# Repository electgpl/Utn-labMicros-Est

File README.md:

Estación Meteorológica Inalámbrica
=============================

### Introducción
 
Se presentará una estación meteorológica inalámbrica hogareña, la misma consta de dos dispositivos individuales, una estación meteorológica interna que provee de valores dentro del recinto donde se encuentra, y una estación meteorológica externa que provee los valores exteriores, entre ambos dispositivos se realiza la telemetría exterior y se muestra en un display alfanumérico en la estación interior, con la finalidad de observar a primera vista los datos meteorológicos internos y externos.
Esta estación funciona de forma inalámbrica con enlaces de radiofrecuencia y funciona con pilas primarias en el caso exterior y batería recargable en el caso interior.

El proyecto surge de la idea de practicar la programación en lenguaje C, los protocolos de comunicación serie y el transporte de los datos vía enlaces inalambricos, en este proyecto se abordará la estructura necesaria para realizar una trama de datos básica, su payload y verificación.
También se realizará la puesta en marcha del sistema mediante electrónica de bajo costo y bajo consumo para afrontar el problema energético que conlleva la utilización de pilas y baterías de forma competitiva con productos comerciales de la actualidad.

----------

----------

### Objetivos
 
- Estación meteorológica con medición interna y externa.
- La estación consiste en un sensor externo y uno interno. 
- El sensor externo posee la capacidad de medir Temperatura, Humedad y Luminosidad. 
- El sensor interno mide Temperatura y Humedad. 
- La telemetría se realiza mediante un enlace inalámbrico simplex UHF, el sensor externo funciona mediante celdas primarias alcalinas y posee electrónica de bajo consumo proporcionando una autonomía de 1 año.
- El sensor interno posee un display de LCD de 2 lineas y 16 caracteres que mostrará la Temperatura y Humedad del sensor interno, la Temperatura, Humedad y Luminosidad del sensor externo.
- El sensor interno cuenta con una batería secundaria de iones de litio recargable mediante un conector micro usb.

> **Nota:**
> - El microcontrolador utilizado se basa en core 8051 (para el cual el firmware se encuentra compilado con Keil sobre un microcontrolador de Silabs C8051F832).
> - Se ha realizado también para Microchip sobre diversas plataformas
> - La simulación se realiza para Microchip sobre Proteus.
> - Los diagramas, PCB y Gerber, son realizados con Eagle.

----------

### Diseño conceptual
 
Para realizar nuestra estación, utilizaremos microcontroladores modernos de bajo consumo y bajo costo, que permite trabajar con una buena autonomía utilizando pilas primarias para aumentar al máximo el rendimiento del sistema.
La estación meteorológica utilizara la función especial del microcontrolador para entrar en modo bajo consumo y así extender la batería.
Una vez en bajo consumo se despertara de forma automática mediante el WDT del microcontrolador cada 10 segundos, se tomará una muestra de temperatura, humedad y luminosidad, se enviará mediante el enlace de RF a la estación interna y luego se volverá a dormir entrando en bajo consumo.
El enlace se ha simplificado al máximo para reducir el costo, se utiliza modulación ASK en UHF mediante oscilador a cristal SAW de 433.92MHz y se enviaran los datos mediante UART invertida a 600bps.
En la estación interior, se utilizara la interrupción de dato presente en UART para atender la telemetría exterior, realizar el parse de la trama y dejarla disponible para la utilización.
Se tomará humedad y temperatura interior, y junto con la telemetría exterior se mostrará todo en un dsiplay LCD de 2x16 caracteres alfanuméricos.
La estación interna cuenta con baterías recargables y su controlador de carga para ser conectado directamente con un cable estándar micro usb.

----------
## Implementación
### Especificaciones de Hardware:
#### Dispositivo Interno:
- Sensor de Temperatura y Humedad, DHT11 (comunicación onWire propietaria).
- Receptor modular RWS simplex UHF operando en la banda de 70cm en 433.92MHz, modulación ASK OOK utilizando protocolo RS232, Antena del tipo microstrip IFA 50 Ohms.
- Display LCD 2x16 con controlador HD44780, para mostrar Temp, Hum, (Interna y Externa), Luminosidad (Externa).
- Cargador de Batería tipo Secundaria Li-Ion con micro USB basado en controlador TP4056, Celda 18650, 4800mAh (típico) .
- Microcontrolador de 8bit Silabs C8051F832.
- Circuito impreso hasta 2 Layer con PTH y tecnologia SMD. 
- Aceptación IPC-356, IPC-600, UL-94.

#### Dispositivo Externo:
- Sensor de Temperatura y Humedad, DHT11 (comunicación onWire propietaria).
- Sensor de Luminosidad basado en LDR con acondicionamiento por firmware.
- Transmisor modular TWS simplex UHF operando en la banda de 70cm en 433.92MHz, modulación ASK OOK utilizando protocolo RS232, Antena del tipo microstrip IFA 50 Ohms.
- Batería del tipo primaria alcalina ZnMnO2 tamaño AA, 2500mAh (típico).
- Microcontrolador de 8bit Silabs C8051F832.
- Circuito impreso hasta 2 Layer con PTH y tecnologia SMD. 
- Aceptación IPC-356, IPC-600, UL-94.

### Especificaciones de Firmware:
El firmware debe contar con estándares de programación, encabezado del programa, descripción, autores, versionado, fechas y referencias.
Las funciones deben contar con los valores de ingreso y egreso a la misma como así el tipo de datos y la descripción de la función.
El programa se realizará en lenguaje C.

- Desarrollo de Bibliotecas necesarias (Estandarizado)
- Pruebas Unitarias de cada Biblioteca con el hardware asociado
- Desarrollo de programa principal
- Manejo de errores
- Creación de diagramas de flujo o estado
- Pruebas Integrados del firmware con todas las Bibliotecas y devices

-------
- Biblioteca para sensor DHT11
>- Manejo de Bus OneWire 5 bytes (4 bytes de datos 1 byte de checksum)
>- Formateo de datos de salida Temperatura: entero sin signo de 8bit
>- Formateo de datos de salida Humedad: entero sin signo de 8bit

- Biblioteca de control del LCD
>- Mapeo de los 2 renglones y 16 caracteres.
>- Control de memoria mediante bus de 4bit y control.
>- Entrada mediante string con control xy de caracteres.

- Biblioteca bitbanging para protocolo manchester en los enlaces UHF
>- BitBanging de del protocolo.
>- Realización de Checksum
>- Salida de datos en formato hexadecimal.
>- Entrada de datos en formato hexadecimal.

- Biblioteca del sensor de luminosidad
>- Utilización del conversor analogico digital provisto por el microcontrolador.
>- Configuración de baja velocidad a resolución de 8bit.
>- Salida datos en formato entero.

- Manejo de Baja Energía
>- Apagado de dispositivos periféricos en desuso mediante transistores NMOS.
>- Reloj WDT para función WakeUp del MCU cada 2.3s
>- Si los datos a medir (sensores) no cambian respecto a la medición anterior, no se enviaran datos repetidos mejorando el consumo.

--------

### Especificaciones Técnicas:

Rango de temperatura 0-50°c (precisión ±2°c) 
Rango de humedad 20-90%RH (precisión ±5％) 
Rango de luminosidad 0-100% (precisión ±20％)    
Rango de trabajo hasta 20m Frecuencia de trabajo 433MHz 
Batería de sensor 2xAA Alcalina 
Vida útil de 2 años 
Batería de cuerpo 1x18650
Vida útil Recargable via USB 
Medidas cuerpo 113x67x27.5mm 
Medidas Sensor 91x70x32.5mm 
Gabinete exterior IPX3 
Este equipo no dispone de protección ATEX, por lo que no debe ser usado en atmósferas potencialmente explosivas (polvo, gases inflamables).

--------

### Conclusiones
 
Se ha logrado implementar una estación meteorológica hogareña de bajo consumo y bajo costo que presenta una propuesta comercial respecto a las competidoras de mismas prestaciones.

Se implementó el código necesario para realizar el proyecto sobre core 8051 bajo una plataforma moderna que opera en 16MHz y 16MIPS.
Se realizó todo el tratamiento de la trama, preámbulo, payload, checksum y parseo de datos para realizar el enlace de telemetría entre los dos dispositivos.
Se analizó la velocidad de transferencia de datos sobre UART para lograr la mejor comunicación y alcance sobre módulos de RF de bajo costo.
Se comprobó el diseño de la antena con la ayuda de instrumental adecuado “VNA” para su correcta adaptación.

--------

### Bibliografía
 
- [1] “Manual 8051 Keil”, 
http://www.keil.com/support/man/docs/is51/
- [2] “Manual Eagle”, 
http://hades.mech.northwestern.edu/images/b/b4/Eagle_Manual.pdf
- [3] “Norma ATEX”, 
http://www.insht.es/InshtWeb/Contenidos/Normativa/GuiasTecnicas/Ficheros/ATM%C3%93SFERAS%20EXPLOSIVAS.pdf
- [4] “Norma IPX3”, 
http://hades.mech.northwestern.edu/images/b/b4/Eagle_Manual.pdfhttp://www.f2i2.net/documentos/lsi/rbt/guias/guia_bt_anexo_1_sep03R1.pdf
- [5] “Norma IPC610”, 
http://www.ipc.org/TOC/IPC-A-610E-Spanish.pdf
- [6] “Datasheet DHT11”, 
https://akizukidenshi.com/download/ds/aosong/DHT11.pdf
- [7] “Datasheet Modulos Transmisor y Receptor RF UHF”, https://4.imimg.com/data4/AJ/NM/MY-1833510/rf-transmitter-receiver-pair-433-mhz-ask.pdf
- [8] “Datasheet LDR”, 
http://kennarar.vma.is/thor/v2011/vgr402/ldr.pdf
- [9] “Datasheet C8051F832 Silabs”, https://www.silabs.com/documents/public/data-sheets/C8051F80x-83x.pdf
- [10] “Datasheet TP4056”, https://dlnmh9ip6v2uc.cloudfront.net/datasheets/Prototyping/TP4056.pdf

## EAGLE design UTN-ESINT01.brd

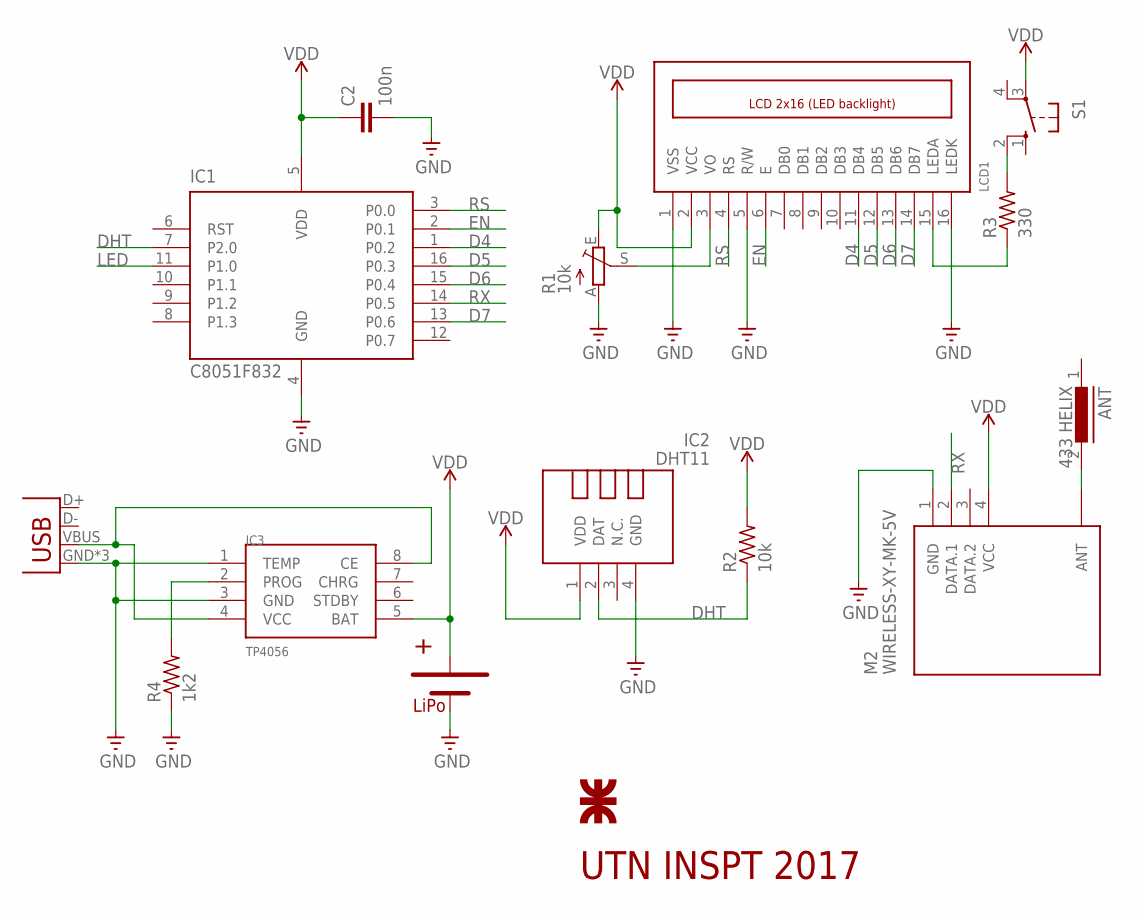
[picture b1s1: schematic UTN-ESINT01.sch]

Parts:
ANT: 433 HELIX; SMSC20
C2: 100n; C050-024X044
IC1: C8051F832; SOIC16R
IC2: DHT11; TEMP-HUM-SENSOR-DHT11
IC3: TP4056; SOP-8
LCD1: LCD_2X16_SIL; HY-1602F
M2: WIRELESS-XY-MK-5V
R1: 10k; B64Y
R2: 10k; 0207/10
R3: 330; 0207/10
R4: 1k2; 0207/10
S1: 10-XX; B3F-10XX
U$3: UTN_LOGO
U$4: LiPo; BATTERYPAD
X1: USB-MICROB

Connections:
D4: IC1.1 (P0.2), LCD1.11 (DB4)
D5: IC1.16 (P0.3), LCD1.12 (DB5)
D6: IC1.15 (P0.4), LCD1.13 (DB6)
D7: IC1.13 (P0.6), LCD1.14 (DB7)
DHT: IC1.7 (P2.0), IC2.2 (DAT), R2.1
EN: IC1.2 (P0.1), LCD1.6 (E)
GND: C2.2, IC1.4 (GND), IC2.4 (GND), IC3.1 (TEMP), IC3.3 (GND), LCD1.1 (VSS), LCD1.5 (R/W), LCD1.16 (LEDK), M2.1 (GND), R1.A, R4.1, U$4.-VE, X1.GND, X1.MT1 (GND), X1.MT2 (GND)
LED: IC1.11 (P1.0)
unnamed: ANT.2, M2.ANT
unnamed: IC3.4 (VCC), IC3.8 (CE), X1.VBUS
unnamed: LCD1.3 (VO), R1.S
unnamed: LCD1.15 (LEDA), R3.1
unnamed: R3.2, S1.2 (S1)
unnamed: IC3.2 (PROG), R4.2
RS: IC1.3 (P0.0), LCD1.4 (RS)
RX: IC1.14 (P0.5), M2.2 (DATA.1)
VDD: C2.1, IC1.5 (VDD), IC2.1 (VDD), IC3.5 (BAT), LCD1.2 (VCC), M2.4 (VCC), R1.E, R2.2, S1.3, U$4.+VE

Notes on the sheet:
UTN INSPT 2017
LiPo

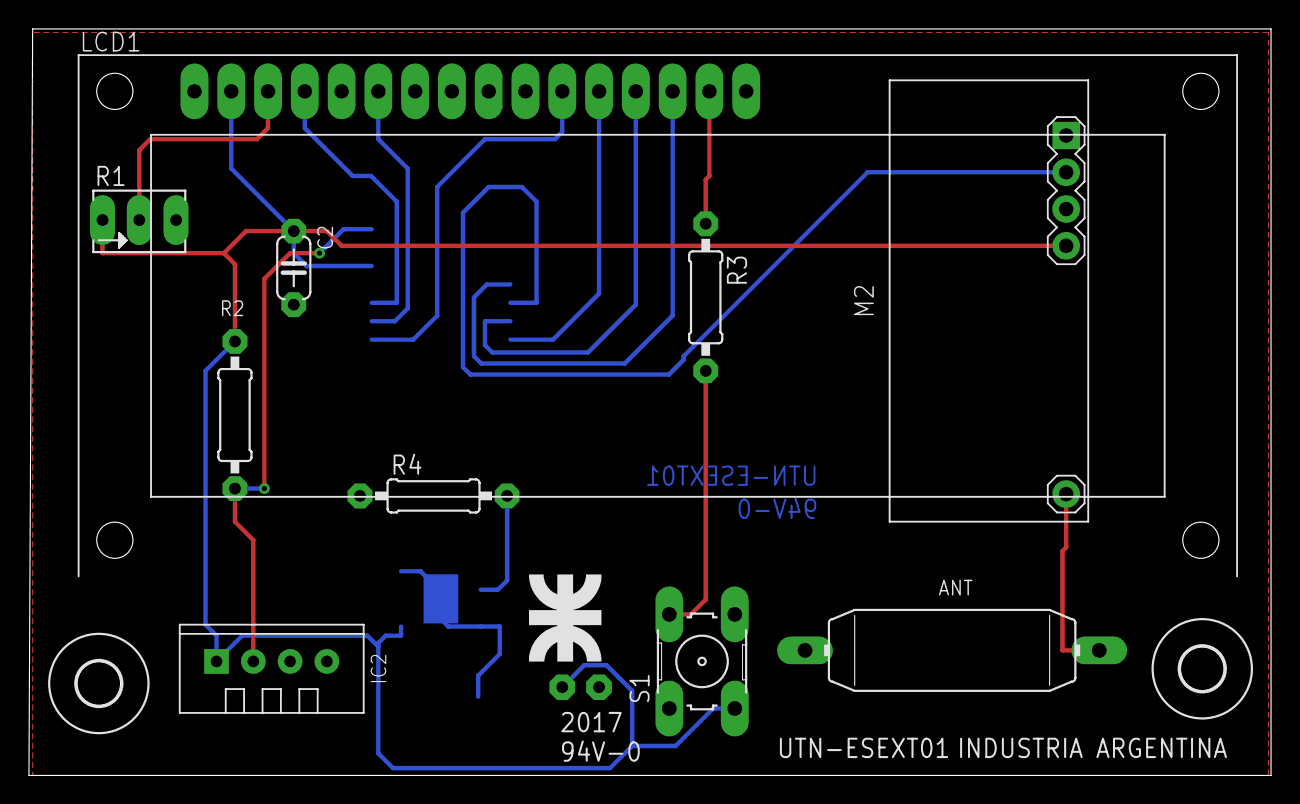
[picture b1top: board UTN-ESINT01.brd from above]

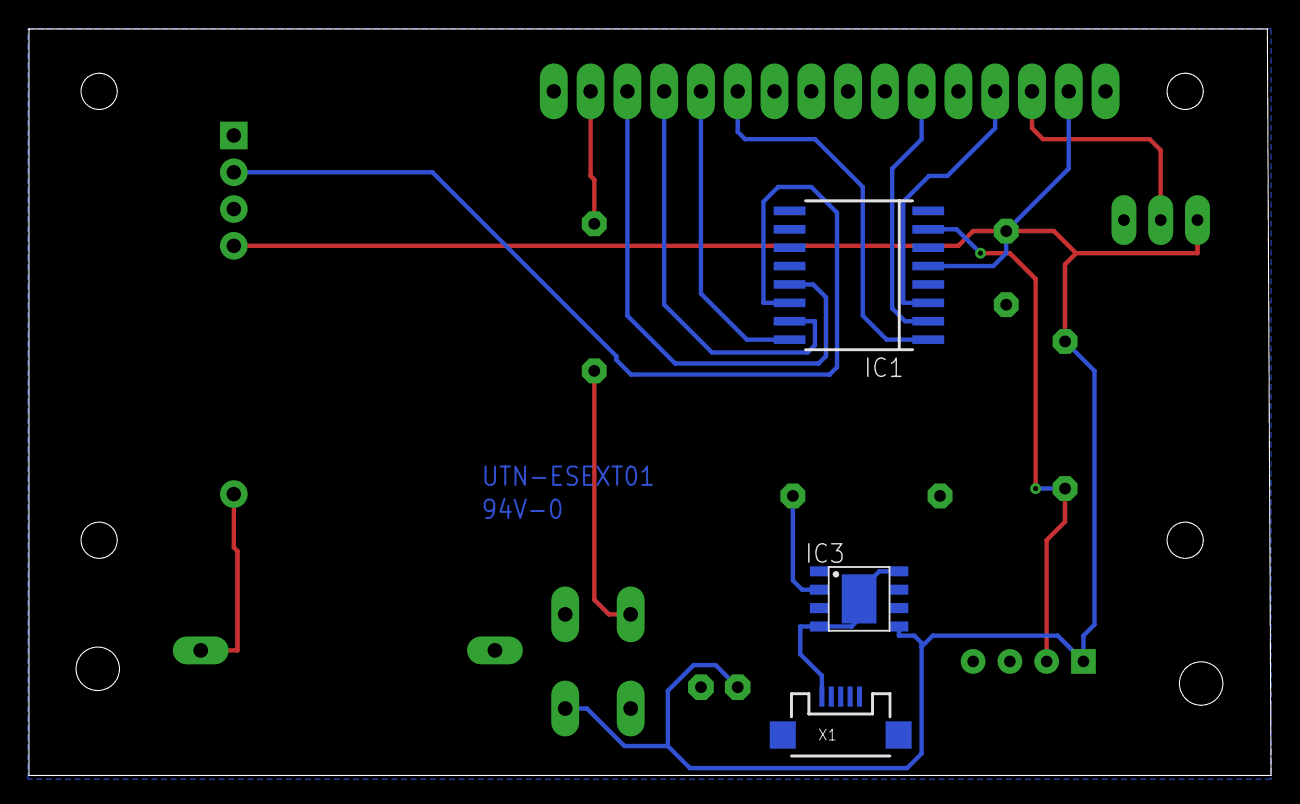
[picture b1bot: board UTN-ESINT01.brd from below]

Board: 2 copper layers, 85.8 x 51.6 mm, 17 parts (3 on the bottom side), 16 nets.

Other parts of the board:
U$1, U$2: 3,0

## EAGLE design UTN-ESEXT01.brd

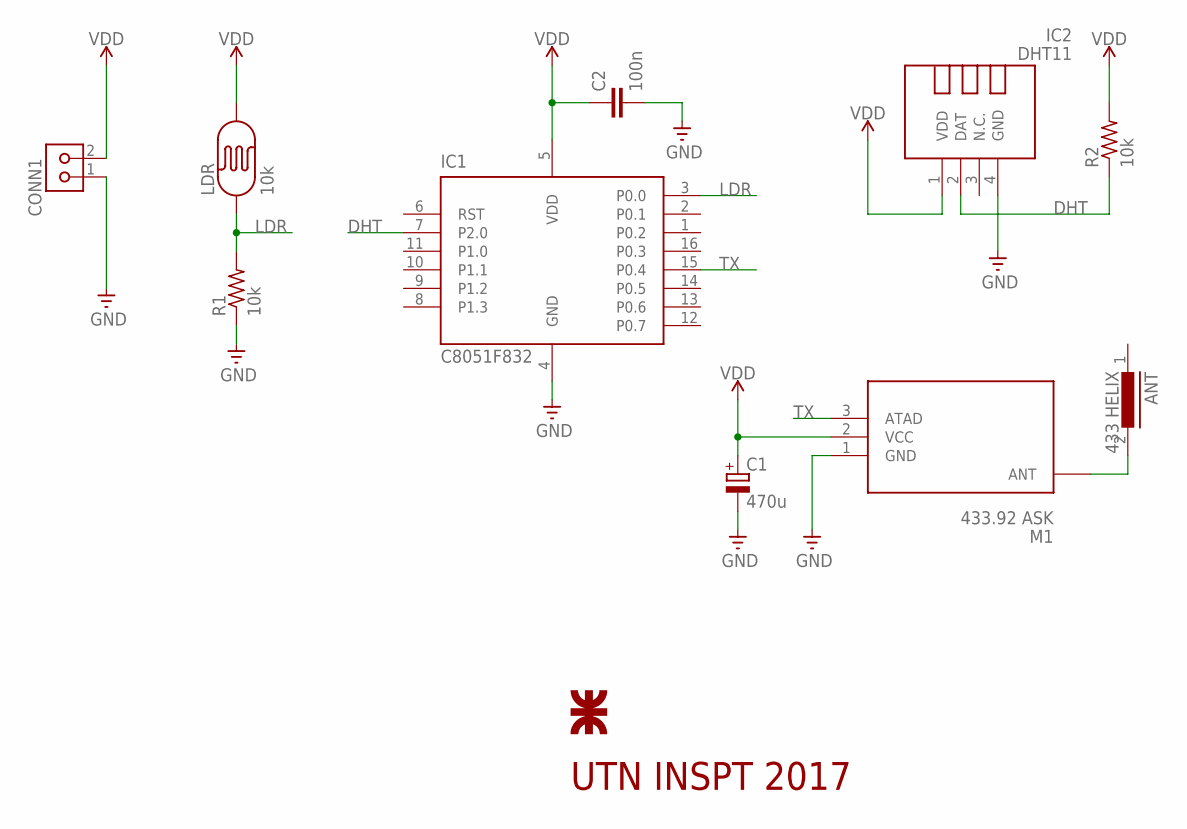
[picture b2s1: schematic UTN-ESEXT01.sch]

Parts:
ANT: 433 HELIX; SMSC20
C1: 470u; E3,5-10
C2: 100n; C050-024X044
CONN1: KK2VSQ; KK-V-2-SQ
IC1: C8051F832; SOIC16R
IC2: DHT11; TEMP-HUM-SENSOR-DHT11
LDR: 10k; ON_BOARD
M1: 433.92 ASK; WIRELESS-XY-FST
R1, R2: 10k; 0207/10
U$3: UTN_LOGO

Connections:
DHT: IC1.7 (P2.0), IC2.2 (DAT), R2.1
GND: C1.-, C2.2, CONN1.1, IC1.4 (GND), IC2.4 (GND), M1.1 (GND), R1.1
LDR: IC1.3 (P0.0), LDR.1, R1.2
unnamed: ANT.2, M1.ANT
TX: IC1.15 (P0.4), M1.3 (ATAD)
VDD: C1.+, C2.1, CONN1.2, IC1.5 (VDD), IC2.1 (VDD), LDR.2, M1.2 (VCC), R2.2

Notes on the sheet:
UTN INSPT 2017

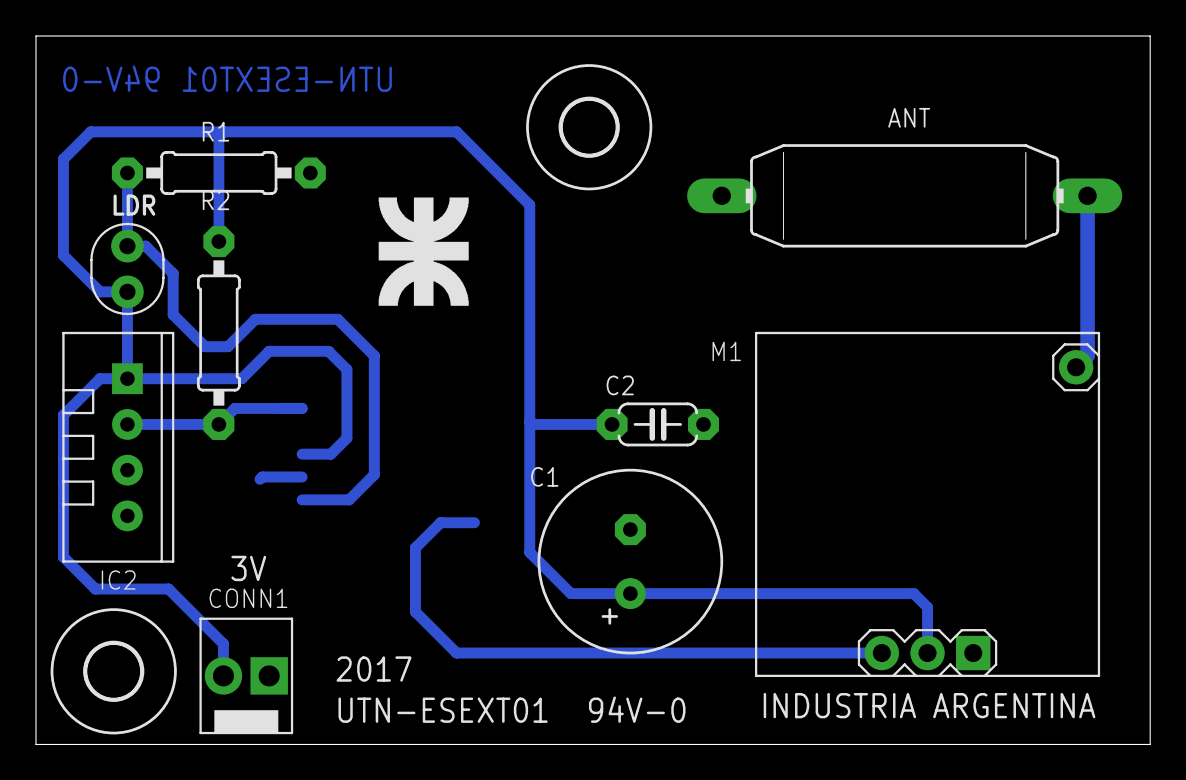
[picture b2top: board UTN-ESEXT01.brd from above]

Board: 2 copper layers, 61.9 x 39.4 mm, 13 parts (1 on the bottom side), 6 nets.

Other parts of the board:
U$1, U$2: 3,0

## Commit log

2017-10-12 Rename 8051 - Estacion Externa Silabs.c to firmware/8051 - Estacion Externa Silabs.c
2017-10-12 Rename 8051 - Estacion Interna Silabs.c to firmware/8051 - Estacion Interna Silabs.c
2017-10-12 Rename Documento Funcional - Estación Meteorológica - Final Entregable.gdoc to documentos/Documento Funcional - Estación Meteorológica - Final Entregable.gdoc
2017-10-12 Rename EQUIPO 3 TP presentado a Steiner.gdoc to documentos/EQUIPO 3 TP presentado a Steiner.gdoc
2017-10-12 Rename Manual de Usuario.gdoc to documentos/Manual de Usuario.gdoc
2017-10-12 Rename PIC - Estación Externa v1 - 1826 - HardTestOK.c to firmware/PIC - Estación Externa v1 - 1826 - HardTestOK.c
2017-10-12 Rename PIC - Estación Interna v1 - 883 - HardTestOK.hex to firmware/PIC - Estación Interna v1 - 883 - HardTestOK.hex
2017-10-12 Rename PIC - Estación Interna v1 - 883 - HardTestOK.c to firmware/PIC - Estación Interna v1 - 883 - HardTestOK.c
2017-10-12 Rename PIC - Estación Externa v1 - 1826 - HardTestOK.hex to firmware/PIC - Estación Externa v1 - 1826 - HardTestOK.hex
2017-10-12 Rename PIC - Estación Externa v1 - 676 - HardTestOK.c to firmware/PIC - Estación Externa v1 - 676 - HardTestOK.c
2017-10-12 Rename PIC - Estación Externa v1 - 676 - HardTestOK.hex to firmware/PIC - Estación Externa v1 - 676 - HardTestOK.hex
2017-10-12 Rename PIC - Estación Interna v1 - 1826 - HardTestOK.c to firmware/PIC - Estación Interna v1 - 1826 - HardTestOK.c
2017-10-12 Rename PIC - Estación Interna v1 - 1826 - HardTestOK.hex to firmware/PIC - Estación Interna v1 - 1826 - HardTestOK.hex
2017-10-12 Rename UTN-ESEXT01.brd to diagramas/UTN-ESEXT01.brd
2017-10-13 Rename UTN-ESINT01.sch to diagramas/UTN-ESINT01.sch
2017-10-13 Rename UTN-ESINT01.dsn to diagramas/UTN-ESINT01.dsn
2017-10-13 Rename UTN-ESINT01.brd to diagramas/UTN-ESINT01.brd
2017-10-13 Rename UTN-ESEXT01.sch to diagramas/UTN-ESEXT01.sch
2017-10-13 Rename diagramas/UTN-ESEXT01.brd to circuitos/UTN-ESEXT01.brd
2017-10-13 Rename diagramas/..UTN-ESEXT01.sch to circuitos/UTN-ESEXT01.sch
2017-10-13 Rename diagramas/UTN-ESINT01.brd to circuitos/UTN-ESINT01.brd
2017-10-13 Rename diagramas/UTN-ESINT01.sch to circuitos/UTN-ESINT01.sch
2017-10-13 Rename diagramas/UTN-ESINT01.dsn to circuitos/UTN-ESINT01.dsn
2017-11-08 modificaciones finales

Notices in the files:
parts and their libraries:
diy-modules: Released under the Creative Commons Attribution 4.0 International License: http://creativecommons.org/licenses/by/4.0
computronics.com.au: ©Computronics Corporation Ltd, 2004
